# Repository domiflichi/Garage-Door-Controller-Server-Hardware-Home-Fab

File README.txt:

This repository contains the Eagle files you can use to manipulate the circuit board
or create gerber files to have your board made by a professional board house. However, 
I recommended using this repository for making the board at home.

For your convenience, I have already created a pdf file of the board that you can use
to print out and use the 'iron-on' method for creating your own single-sided board:
GarageDoorController-v10.pdf

When assembling your board, I have provided an additional pdf for your reference:
GarageDoorController-v10AssemblyReference.pdf

If you want to send gerber files off to a board house, I highly recommend using my 
other repository:
https://github.com/domiflichi/Garage-Door-Controller-Server-Hardware-Pro-Fab

For more information and instructions on how to set all of this up and how everything works
together, please visit the home page of the project on my website:
http://jamienerd.blogspot.com/2013/12/garage-door-controller-tutorial.html

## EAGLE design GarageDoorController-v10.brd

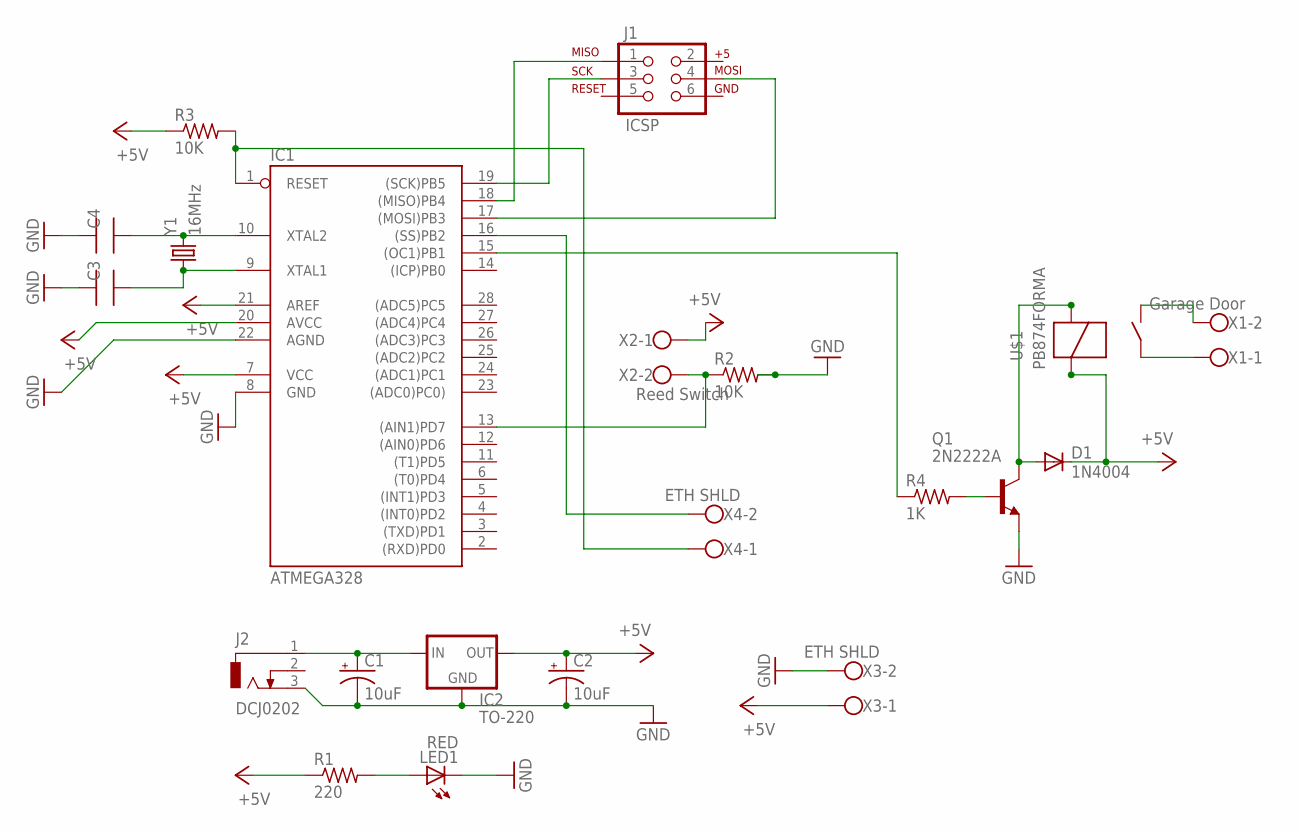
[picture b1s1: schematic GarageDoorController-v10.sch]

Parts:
C1, C2: 10uF; E2-5
C3, C4: 1440PH
D1: 1N4004; DO41-10
IC1: ATMEGA328; DIL28-3
IC2: TO-220; TO-220-ALT
J1: ICSP; 2X3
J2: DCJ0202
LED1: RED; LED5MM
Q1: 2N2222A; TO18
R1: 220; 0204/7
R2, R3: 10K; 0204/7
R4: 1K; 0204/7
U$1: PB874FORMA; PB874
X1: Garage Door; W237-102
X2: Reed Switch; W237-102
X3, X4: ETH SHLD; W237-102
Y1: 16MHz; HC49US

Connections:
+5V: C2.+, D1.C, IC1.7 (VCC), IC1.20 (AVCC), IC1.21 (AREF), IC2.OUT, R1.1, R3.1, U$1.2, X2.1, X3.1
GND: C1.-, C2.-, C3.1, C4.1, IC1.8 (GND), IC1.22 (AGND), IC2.GND, J2.3, LED1.K (C), Q1.1 (E), R2.2, X3.2
unnamed: C4.2, IC1.10 (XTAL2), Y1.2
unnamed: C3.2, IC1.9 (XTAL1), Y1.1
unnamed: C1.+, IC2.IN, J2.1
unnamed: LED1.A, R1.2
unnamed: IC1.1 (RESET), R3.2, X4.1
unnamed: IC1.19 ((SCK)PB5), J1.3
unnamed: IC1.18 ((MISO)PB4), J1.1
unnamed: IC1.17 ((MOSI)PB3), J1.4
unnamed: Q1.2 (B), R4.2
unnamed: IC1.13 ((AIN1)PD7), R2.1, X2.2
unnamed: D1.A, Q1.3 (C), U$1.1
unnamed: U$1.4, X1.2
unnamed: IC1.15 ((OC1)PB1), R4.1
unnamed: U$1.3, X1.1
unnamed: IC1.16 ((SS)PB2), X4.2

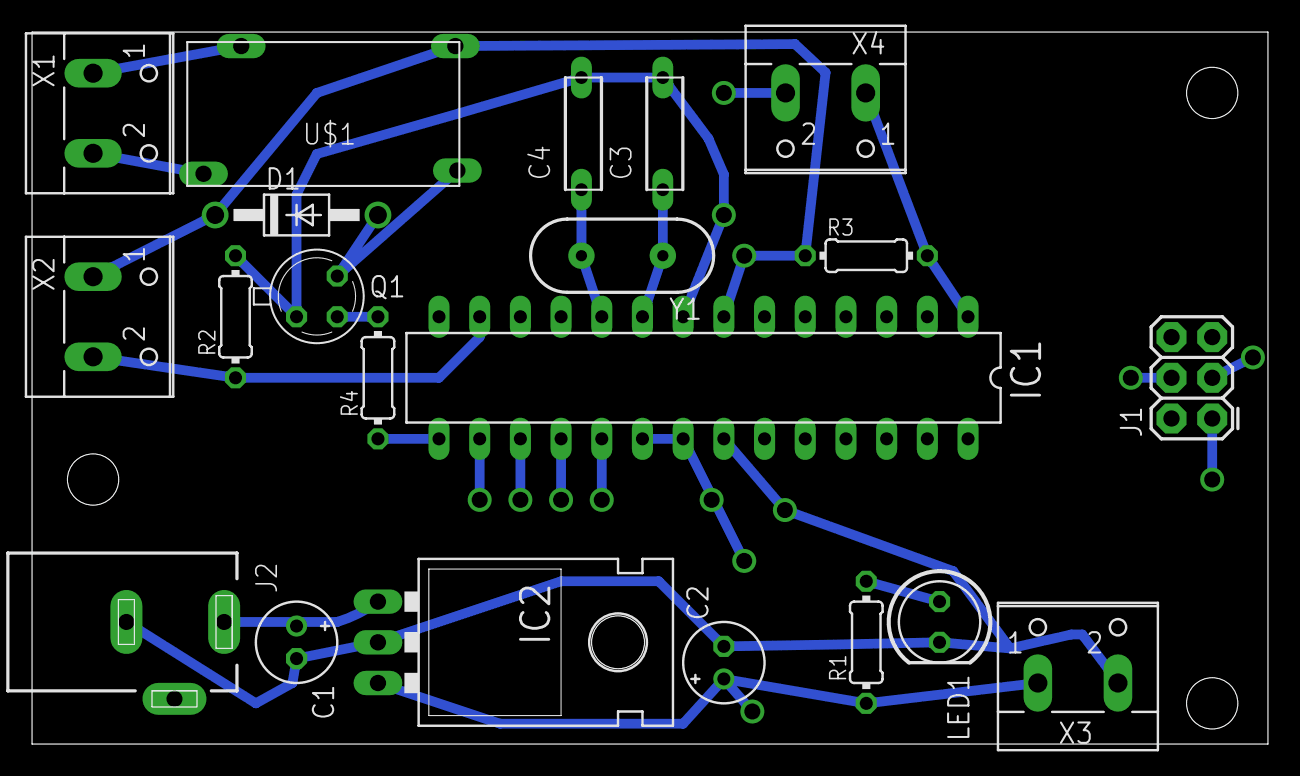
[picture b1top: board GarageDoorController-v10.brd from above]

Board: 2 copper layers, 77.1 x 44.4 mm, 21 parts (0 on the bottom side), 17 nets.

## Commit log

2012-12-01 Initial Commit 12/1/2012
    This is just before making 2 separate board files - 1 for single-sided
    (for home manufacturing) and one for double-sided board (for sending
    to a board house)
2012-12-01 GarageDoorController-v10.brd file should be ready for home fabrication.
2012-12-02 Fixed the pin locations of the relay, added 'Thumbs.db' to .gitignore.
2012-12-24 Modified GarageDoorController-v10.brd file: Shrunk overall board size, moving parts around, closer together.
2012-12-25 Modified GarageDoorController-v10.brd file: The 'X4' text was mirrored, so corrected that. Added 'GDC v1.0' text on the '27 tValues' layer. Changed the 'JamieNerd.blogspot.com' text to the '27 tValue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
2013-01-01 Added new file:
    GarageDoorController-v10.pdf - file ready to use for home fabrication
2013-01-01 Added new file:
    README.txt
2013-01-01 Added new file: GarageDoorController-v10AssemblyReference.pdf
    Update file:
    README.txt - referenced above file for assembling board
2013-12-30 Updated README.TXT: Added correct project URL

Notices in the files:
parts and their libraries:
SparkFun-FreqCtrl: Licensing: CC v3.0 Share-Alike You are welcome to use this library for commercial purposes.
